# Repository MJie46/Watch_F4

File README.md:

# Watch_F4
>
#### 尺寸 40x36mm
#### STM32F405RGT6
#### IP5306+MP20045
#### MPU6050
#### W25Q128JVS
#### 蓝牙主从一体模块
#### 1.44寸SPI屏
#### 背面MAX30102，用作血氧检测
#### 背面引出4个按钮引脚

### 3D打印外壳
##### 本来想做成像外面卖的智能手表使用触电充电，再配上一个充电的底壳，但尝试后发现手工焊接接触平面很难4个触点在同一平面上，改用type-c接口，通过type-c烧录和串口调试

####第一版做好的大概，码代码中...

### 系统FreeRTOS，具体功能还没完善，待填...

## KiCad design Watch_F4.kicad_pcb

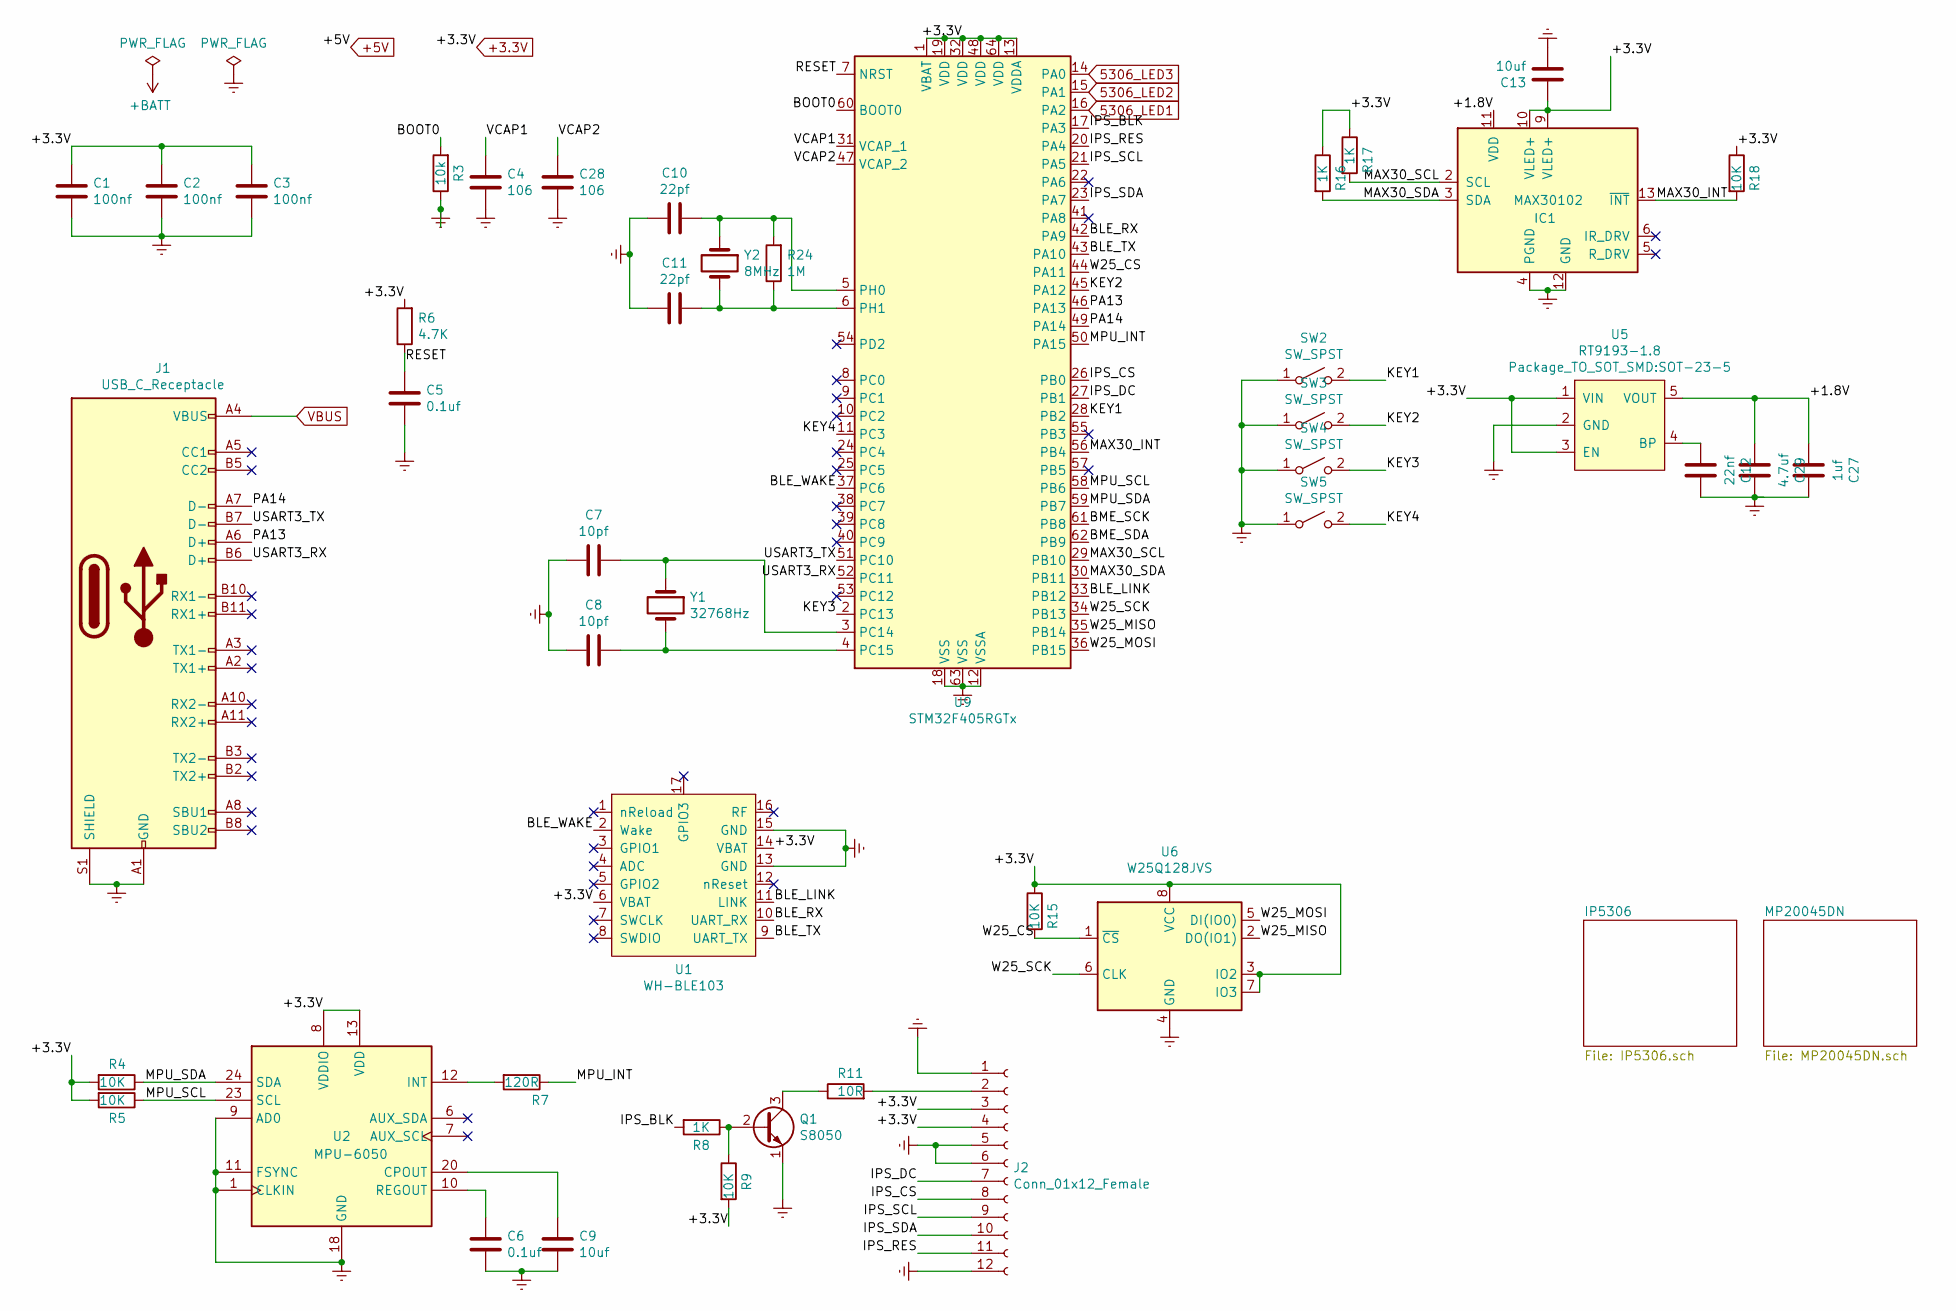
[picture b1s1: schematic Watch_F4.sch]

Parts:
C1, C2, C3: 100nf; C_0603_1608Metric_Pad1.05x0.95mm_HandSolder
C4, C28: 106; C_0603_1608Metric_Pad1.05x0.95mm_HandSolder
C5, C6: 0.1uf; C_0603_1608Metric_Pad1.05x0.95mm_HandSolder
C7, C8: 10pf; C_0603_1608Metric_Pad1.05x0.95mm_HandSolder
C9, C13: 10uf; C_0603_1608Metric_Pad1.05x0.95mm_HandSolder
C10, C11: 22pf; C_0603_1608Metric_Pad1.05x0.95mm_HandSolder
C12: 22nf; C_0603_1608Metric_Pad1.05x0.95mm_HandSolder
C27: 1uf; C_0603_1608Metric_Pad1.05x0.95mm_HandSolder
C29: 4.7uf; C_0603_1608Metric_Pad1.05x0.95mm_HandSolder
IC1: MAX30102; Maxim_OLGA-14_3.3x5.6mm_P0.8mm
J1: USB_C_Receptacle; USB_C_Receptacle_XKB_U262-16XN-4BVC11
J2: Conn_01x12_Female; FPC1x12-0.7
Q1: S8050; SOT-23-s8050
R3: 10k; R_0603_1608Metric_Pad1.05x0.95mm_HandSolder
R4, R5, R9, R15, R18: 10K; R_0603_1608Metric_Pad1.05x0.95mm_HandSolder
R6: 4.7K; R_0603_1608Metric_Pad1.05x0.95mm_HandSolder
R7: 120R; R_0603_1608Metric_Pad1.05x0.95mm_HandSolder
R8, R16, R17: 1K; R_0603_1608Metric_Pad1.05x0.95mm_HandSolder
R11: 10R; R_0603_1608Metric_Pad1.05x0.95mm_HandSolder
R24: 1M; R_0603_1608Metric_Pad1.05x0.95mm_HandSolder
SW2, SW3, SW4, SW5: SW_SPST; SW_SPST_PTS645
U1: WH-BLE103
U2: MPU-6050; InvenSense_QFN-24_4x4mm_P0.5mm
U5: RT9193-1.8; SOT-23-5
U6: W25Q128JVS; SOIC-8_5.23x5.23mm_P1.27mm
U9: STM32F405RGTx; LQFP-64_10x10mm_P0.5mm
Y1: 32768Hz; Crystal_SMD_3215-2Pin_3.2x1.5mm
Y2: 8MHz; Crystal_SMD_TXC_7A-2Pin_5x3.2mm

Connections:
5306_LED1: U9.16 (PA2); also elsewhere on the board
5306_LED2: U9.15 (PA1); also elsewhere on the board
5306_LED3: U9.14 (PA0); also elsewhere on the board
+3.3V: C1.1, C2.1, C3.1, C13.1, IC1.9 (VLED+), IC1.10 (VLED+), J2.3, J2.4, R4.2, R5.2, R6.2, R9.2, R15.1, R16.1, R17.1, R18.1, U1.6 (VBAT), U1.14 (VBAT), U2.8 (VDDIO), U2.13 (VDD), U5.1 (VIN), U5.3 (EN), U6.3 (IO2), U6.7 (IO3), U6.8 (VCC), U9.1 (VBAT), U9.13 (VDDA), U9.19 (VDD), U9.32 (VDD), U9.48 (VDD), U9.64 (VDD); also elsewhere on the board
/+1.8V: C27.2, C29.2, IC1.11 (VDD), U5.5 (VOUT)
/BLE_LINK: U1.11 (LINK), U9.33 (PB12)
/BLE_RX: U1.10 (UART_RX), U9.42 (PA9)
/BLE_TX: U1.9 (UART_TX), U9.43 (PA10)
/BLE_WAKE: U1.2 (Wake), U9.37 (PC6)
/BME_SCK: U9.61 (PB8)
/BME_SDA: U9.62 (PB9)
/BOOT0: R3.2, U9.60 (BOOT0)
/IPS_BLK: R8.2, U9.17 (PA3)
/IPS_CS: J2.8, U9.26 (PB0)
/IPS_DC: J2.7, U9.27 (PB1)
/IPS_RES: J2.11, U9.20 (PA4)
/IPS_SCL: J2.9, U9.21 (PA5)
/IPS_SDA: J2.10, U9.23 (PA7)
/KEY1: SW2.2 (B), U9.28 (PB2)
/KEY2: SW3.2 (B), U9.45 (PA12)
/KEY3: SW4.2 (B), U9.2 (PC13)
/KEY4: SW5.2 (B), U9.11 (PC3)
/MAX30_INT: IC1.13 (~INT), R18.2, U9.56 (PB4)
/MAX30_SCL: IC1.2 (SCL), R17.2, U9.29 (PB10)
/MAX30_SDA: IC1.3 (SDA), R16.2, U9.30 (PB11)
/MPU_INT: R7.1, U9.50 (PA15)
/MPU_SCL: R5.1, U2.23 (SCL), U9.58 (PB6)
/MPU_SDA: R4.1, U2.24 (SDA), U9.59 (PB7)
/PA13: J1.A6 (D+), U9.46 (PA13)
/PA14: J1.A7 (D-), U9.49 (PA14)
/RESET: C5.1, R6.1, U9.7 (NRST)
/UART4_RX: J1.B6 (D+), U9.52 (PC11)
/UART4_TX: J1.B7 (D-), U9.51 (PC10)
/VCAP1: C4.1, U9.31 (VCAP_1)
/VCAP2: C28.1, U9.47 (VCAP_2)
/W25_CS: R15.2, U6.1 (~CS), U9.44 (PA11)
/W25_MISO: U6.2 (DO(IO1)), U9.35 (PB14)
/W25_MOSI: U6.5 (DI(IO0)), U9.36 (PB15)
/W25_SCK: U6.6 (CLK), U9.34 (PB13)
Earth: C1.2, C2.2, C3.2, C4.2, C5.2, C6.2, C7.2, C8.2, C9.2, C10.2, C11.2, C12.1, C13.2, C27.1, C28.2, C29.1, IC1.4 (PGND), IC1.12 (GND), J1.A1 (GND), J1.A12 (GND), J1.B1 (GND), J1.B12 (GND), J1.S1 (SHIELD), J2.1, J2.5, J2.6, J2.12, Q1.1 (E), R3.1, SW2.1 (A), SW3.1 (A), SW4.1 (A), SW5.1 (A), U1.13 (GND), U1.15 (GND), U2.1 (CLKIN), U2.9 (AD0), U2.11 (FSYNC), U2.18 (GND), U5.2 (GND), U6.4 (GND), U9.12 (VSSA), U9.18 (VSS), U9.63 (VSS); also elsewhere on the board
unnamed: C6.1, U2.10 (REGOUT)
unnamed: C7.1, U9.3 (PC14), Y1.1
unnamed: C8.1, U9.4 (PC15), Y1.2
unnamed: C9.1, U2.20 (CPOUT)
unnamed: C10.1, R24.2, U9.5 (PH0), Y2.1
unnamed: C11.1, R24.1, U9.6 (PH1), Y2.2
unnamed: C12.2, U5.4 (BP)
unnamed: J2.2, R11.2
unnamed: Q1.2 (B), R8.1, R9.1
unnamed: Q1.3 (C), R11.1
unnamed: R7.2, U2.12 (INT)
VBUS: J1.A4 (VBUS), J1.A9 (VBUS), J1.B4 (VBUS), J1.B9 (VBUS); also elsewhere on the board

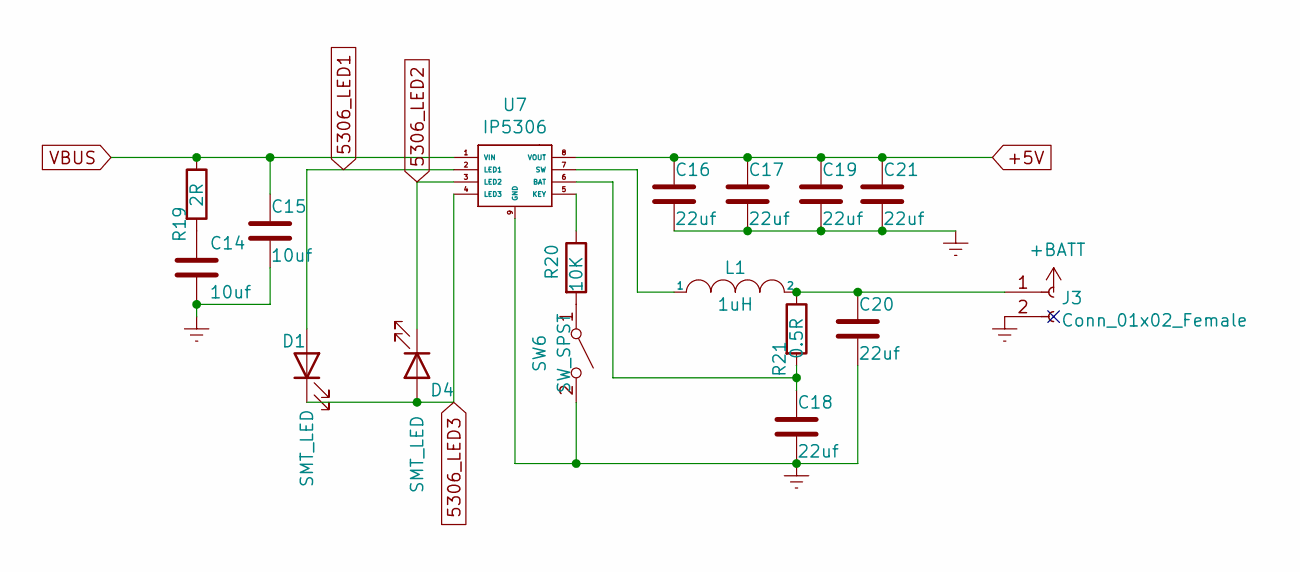
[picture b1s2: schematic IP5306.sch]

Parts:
C14, C15: 10uf; C_0603_1608Metric_Pad1.05x0.95mm_HandSolder
C16, C17, C18, C19, C20, C21: 22uf; C_0603_1608Metric_Pad1.05x0.95mm_HandSolder
D1, D4: SMT_LED; LED_0603_1608Metric
J3: Conn_01x02_Female; PinSocket_1x02_P2.00mm_Vertical
L1: 1uH; L_Wuerth_HCI-7030
R19: 2R; R_0603_1608Metric_Pad1.05x0.95mm_HandSolder
R20: 10K; R_0603_1608Metric_Pad1.05x0.95mm_HandSolder
R21: 0.5R; R_0603_1608Metric_Pad1.05x0.95mm_HandSolder
SW6: SW_SPST; SW_Push_SPST_NO_Alps_SKRK
U7: IP5306; SOIC-8-1EP_3.9x4.9mm_P1.27mm_EP2.29x3mm

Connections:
5306_LED1: D1.2 (A), U7.2 (LED1); also elsewhere on the board
5306_LED2: D4.1 (K), U7.3 (LED2); also elsewhere on the board
5306_LED3: D1.1 (K), D4.2 (A), U7.4 (LED3); also elsewhere on the board
+5V: C16.1, C17.1, C19.1, C21.1, U7.8 (VOUT); also elsewhere on the board
Earth: C14.2, C15.2, C16.2, C17.2, C18.2, C19.2, C20.2, C21.2, J3.2, SW6.2 (B), U7.9 (GND); also elsewhere on the board
unnamed: C14.1, R19.2
unnamed: C18.1, R21.2, U7.6 (BAT)
unnamed: C20.1, J3.1, L1.2, R21.1
unnamed: L1.1, U7.7 (SW)
unnamed: R20.1, U7.5 (KEY)
unnamed: R20.2, SW6.1 (A)
VBUS: C15.1, R19.1, U7.1 (VIN); also elsewhere on the board

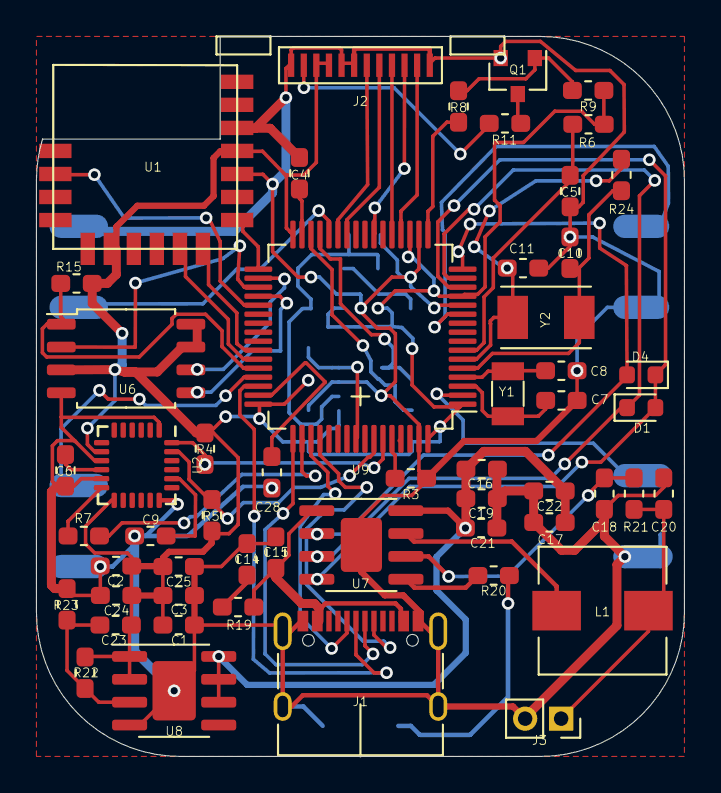
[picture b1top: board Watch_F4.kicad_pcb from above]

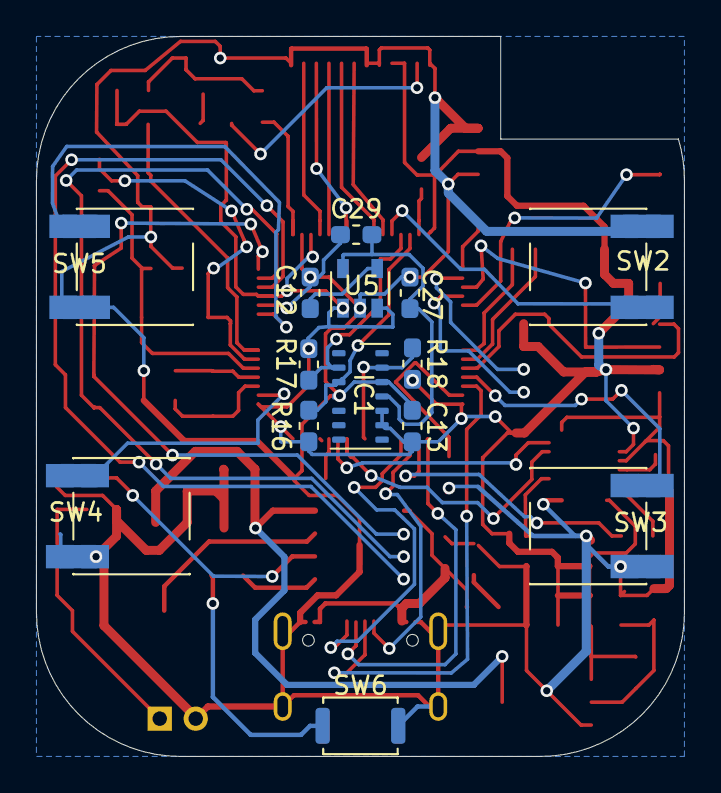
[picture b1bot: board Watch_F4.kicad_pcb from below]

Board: 2 copper layers, 36.0 x 40.0 mm, 68 parts (14 on the bottom side), 58 nets.

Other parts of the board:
C22, C24: 2.2uf; C_0603_1608Metric_Pad1.05x0.95mm_HandSolder
C23: 100pf; C_0603_1608Metric_Pad1.05x0.95mm_HandSolder
C25: 1uf; C_0603_1608Metric_Pad1.05x0.95mm_HandSolder
R22: 12K; R_0603_1608Metric_Pad1.05x0.95mm_HandSolder
R23: 10K; R_0603_1608Metric_Pad1.05x0.95mm_HandSolder
U8: MP20045; SOIC-8-1EP_3.9x4.9mm_P1.27mm_EP2.41x3.3mm

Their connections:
+3.3V: C23.1, C24.1, C25.1, R22.2, U8.1, U8.2; also elsewhere on the board
+5V: C22.1, U8.6, U8.7, U8.8; also elsewhere on the board
Earth: C22.2, C24.2, C25.2, R23.1, U8.4, U8.9; also elsewhere on the board
unnamed: C23.2, R22.1, R23.2, U8.3

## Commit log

2020-11-02 更新README,图片
